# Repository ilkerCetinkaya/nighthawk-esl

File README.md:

# NIGHTHAWK: ESL security research instrument (KiCad hardware, firmware, AI-assisted routing)

**Role: Hardware and firmware designer** · Nov 2026 to present · work in progress

> 🇹🇷 **Özet:** NIGHTHAWK, elektronik raf etiketi (ESL) sistemlerinin güvenlik araştırması için tasarladığım taşınabilir bir ölçüm cihazı. REV A (ESP32-C3 + iki RF genişleme yuvası) şematik ve PCB olarak tamamlandı, üretilmedi. REV B, tek kartta 2.4 GHz + 868 MHz + 13.56 MHz NFC + IR bağlantısını birleştiren 80×50 mm, 4 katmanlı bir tasarım: şematik ve yerleşim tamam, **yönlendirme (routing) henüz tamamlanmadı**. Hiçbir kart üretilmedi, güç verilmedi, ölçülmedi. Bu depo her şeyi (şematikler, üretici betikleri, mühendislik raporları, firmware, masaüstü uygulaması ve AI destekli routing altyapısı) dürüst durum notlarıyla birlikte içerir.

> **Status, stated plainly:** nothing in this repository has been fabricated, powered up or measured. Every antenna, RF-matching and coexistence number is a datasheet value, a hand calculation or an assumption, and is labelled that way in the documents. No claim of antenna performance, RF compliance or production readiness is made. REV B routing is **not finished**, and the only REV B Gerber set published is an explicitly **unrouted, non-functional** one (see "REV B manufacturing files").

## What it is

A bench instrument for studying electronic shelf label (ESL) links on equipment you own, with the radio paths kept measurable (U.FL test points, tunable matching networks) and a **hardware interlock that keeps every RF path off by default**.

**Intended use:** owned equipment only, conducted or shielded testing, passive measurement. The firmware refuses to start a session when the hardware interlock is open. The repository contains **no ESL command generation** and no attack code; the research documents are desk research from public sources.

| Revision | State | What it is |
|---|---|---|
| **REV A** | schematic and PCB complete, ERC 0 violations, DRC 0 errors, not fabricated | ESP32-C3-WROOM-02 main board, two modular RF expansion slots, passive RF test path, hardware interlock |
| **REV B** | schematic and placement done, **routing in progress** | one integrated 80×50 mm 4-layer board: ESP32-C3, TI CC1352R (2.4 GHz and 868 MHz), TRF7970A NFC, 940 nm IR link, hardware interlock |

## REV B at a glance

| Block | Parts |
|---|---|
| **Controller** | ESP32-C3-WROOM-02 (on-board antenna keepout per Espressif, 15 mm) |
| **Sub-GHz and 2.4 GHz radio** | TI CC1352R1F3RGZR, Johanson 0900PC15A0036 IPC (2.4 GHz and sub-GHz from one RF port pair), 868 MHz chip antenna, 2.4 GHz inverted-F antenna (TI AN043 geometry), U.FL test connectors, tunable pi/L matching networks |
| **NFC** | TI TRF7970A, 18×16 mm 6-turn PCB coil (calculated 1.43 µH, not measured) |
| **Optical link** | 940 nm IR LED and photodiode |
| **Power** | LiPo, BQ24074 charger, TPS63802 buck-boost, USB-C |
| **Safety** | hardware interlock (default RF off), independent RF power gating, ESP32 to CC1352R time-slot coordination lines |
| **Fabrication target** | JLCPCB JLC04161H-7628 4-layer stackup, black mask, HASL with lead, cost-optimised |

<p align="center"><em>REV B 3D renders from KiCad (preliminary placement, not routed).</em></p>

### Engineering approach

Every document labels its evidence: **[DS]** manufacturer datasheet read, **[CALC]** calculation (script included), **[ASM]** assumption, **[MEAS]** measurement (none exist yet). Highlights:

- **Component gate and passive selection** for every RF part, with the datasheet pages used ([`REV_B_COMPONENT_GATE.md`](RevB/REV_B_COMPONENT_GATE.md), [`REV_B_PASSIVE_SELECTION.md`](RevB/REV_B_PASSIVE_SELECTION.md)).
- **RF design gate**: ESP32 to CC1352R coexistence, CC1352R input-power protection margins on a no-loss basis (the 1.3 dB discrepancy between two earlier tables is explained), 868 MHz corner keepout, NFC coil guidance, feed-line stackup ([`REV_B_RF_DESIGN_GATE.md`](RevB/REV_B_RF_DESIGN_GATE.md)).
- **Pre-routing resolutions**: USB-C and Johanson IPC footprints rebuilt from manufacturer drawings, battery connector and shield-frame dimensions checked ([`REV_B_PRE_ROUTING_RESOLUTIONS.md`](RevB/REV_B_PRE_ROUTING_RESOLUTIONS.md)).
- **Antenna design notes** with the TI AN043 inverted-F geometry and its keepouts on all four layers ([`REV_B_ANTENNA_ENGINEERING_R2.md`](RevB/REV_B_ANTENNA_ENGINEERING_R2.md)).
- **Mandatory prototype measurements** are listed rather than assumed away: S21 of the IPC path before the first transmission, antenna return loss, coil inductance and Q, time-slot coexistence.

### Routing status (honest)

- **Done and DRC-clean:** RF paths routed programmatically (`RevB/pcb/rf_route_b.py`): CC1352R to IPC differential pairs, both antenna feed chains with matching-network nodes, U.FL taps, ground vias. The 868 MHz feed uses a short B.Cu hop where the 2.4 GHz and sub-GHz feeds would otherwise cross.
- **Not done:** the rest of the board. With **In1 kept as a pure GND reference plane**, Freerouting 2.5.0 leaves about 200 nets unrouted on the current placement; allowing it to route on In1 reaches ~85 unrouted but breaks the plane, which is not acceptable here. The honest options are a looser placement or a larger board; that is a design decision still open.
- **Controlled impedance is not claimed.** The 50 Ω width (0.359 mm over L2, calculator result for the JLC stackup) is a number, not a validated geometry; the 2.4 GHz diff-pair necks are not 50 Ω.

## AI-assisted routing infrastructure (`RevB/ai_routing/`)

An experiment in driving KiCad and an autorouter through MCP, with engineering-grade checks instead of trust in the autorouter.

- **kicad-mcp-pro 4.9.0** and the **official Freerouting 2.5.0 MCP server**, run locally and offline (no design data leaves the machine).
- Tested on a copy, on a 16-net subset: both paths completed 20 of 20 connections (about 126 mm, 17 vias), **but** the router drew signal tracks on the GND plane and ignored custom DRC rules. Full report: [`RevB/ai_routing/REPORT.md`](RevB/ai_routing/REPORT.md).
- Problems found and documented: KiCad 10.0.6's CLI has no headless DSN export (pcbnew's Python API is used), kicad-mcp-pro's Freerouting command adds a `-drc` flag that makes 2.5.0 skip routing, Freerouting's MCP advertises an `outputSchema` but returns no `structuredContent` (a wrapper strips it), and one environment variable made kicad-mcp-pro hang at start-up.
- Recommended architecture: RF paths scripted and locked, the rest routed by class, and a gate that fails if any signal track appears on the GND plane.
- Handshake evidence and the continuing plan: `RevB/ai_routing/results/handshake_evidence.md`, `RevB/ai_routing/HANDOFF_PHASES.md`.

## Repository layout

| Path | Contents |
|---|---|
| `Hardware/` | REV A KiCad project (`NIGHTHAWK.kicad_pro`, 11 sheets, PCB) and `build/` generator scripts (`design.py` is the single source of parts and nets) |
| `Firmware/` | PlatformIO + ESP-IDF project: CLI over USB, interlock monitor, I/O expander, ADC, microSD, device database. Not compiled on hardware |
| `Software/desktop_app/` | PySide6 companion app |
| `Documentation/` | REV A reports, pin assignment, parts verification, race and watchdog reviews, `Research/` (ESL protocol desk research, TagTinker review, licence audit) |
| `RevB/` | REV B design documents, `schematic/` (7 sheets, generator scripts), `pcb/` (board generator, RF routing, routing and verification scripts), `integrated/` (RF calculations), `ai_routing/` |
| `README_REV_A.md` | the original REV A readme |

REV A manufacturing outputs and bulky generated test boards are deliberately not published. REV B has an **unrouted, non-functional** JLCPCB set under `RevB/manufacturing/` (see below).

## REV B manufacturing files (unrouted, non-functional)

`RevB/manufacturing/JLCPCB_REVB_UNROUTED/` holds the Gerber zip, a JLCPCB BOM with LCSC numbers (181 parts, none invented) and a CPL with corrected rotations, generated by `RevB/manufacturing/make_fab_b.py` from the board as it stands. **The board is not routed (409 unconnected connections), so these files would produce a non-working PCB.** They were generated on request to exercise the fabrication pipeline.

- CPL rotation: KiCad angle, bottom side `(180 - angle) mod 360`, plus package corrections from the community JLCKicadTools database (not an official JLCPCB table). Polarised parts without a matching rule (ESP32 module, CC1352R, TRF7970A, LEDs, crystals, IR parts, USB-C) must be checked in the JLCPCB preview.
- Parts without an LCSC number (Johanson IPC, shield frame and others) and all DNP matching parts are listed separately in `NOT_ASSEMBLED_BY_JLCPCB.csv`.
- Placement was loosened (0.6 mm extra courtyard gap, more use of the bottom side) to try to route with In1 kept as a pure GND plane; Freerouting still left roughly 110 to 140 connections open. Details in `RevB/ai_routing/REPORT.md`.

## Rebuild (REV B)

Run with KiCad 10's bundled Python:

```
cd RevB/schematic && python3 gen_footprints_b.py && python3 gen_sch_b.py
cd ../pcb && python3 make_board_b.py      # board with placement
python3 rf_route_b.py                      # programmatic RF routing
python3 verify_r2.py                       # keepout verification on all layers
```

## What is not done

Routing of the full REV B board · antenna and matching validation · any measurement · firmware on hardware · a releasable (routed, reviewed) REV B Gerber set · RF compliance. Each of these is an open item, not a hidden assumption.

---

*Product and component names belong to their owners (Espressif, Texas Instruments, Johanson Technology, Würth Elektronik, JST, JLCPCB and others). The research notes cite public sources (Furrtek, PrecIR, TagTinker); their licences are audited in `Documentation/Research/REUSE_AND_LICENSE_AUDIT.md`. No licence is granted for this repository yet; all rights reserved by the author until one is chosen.*

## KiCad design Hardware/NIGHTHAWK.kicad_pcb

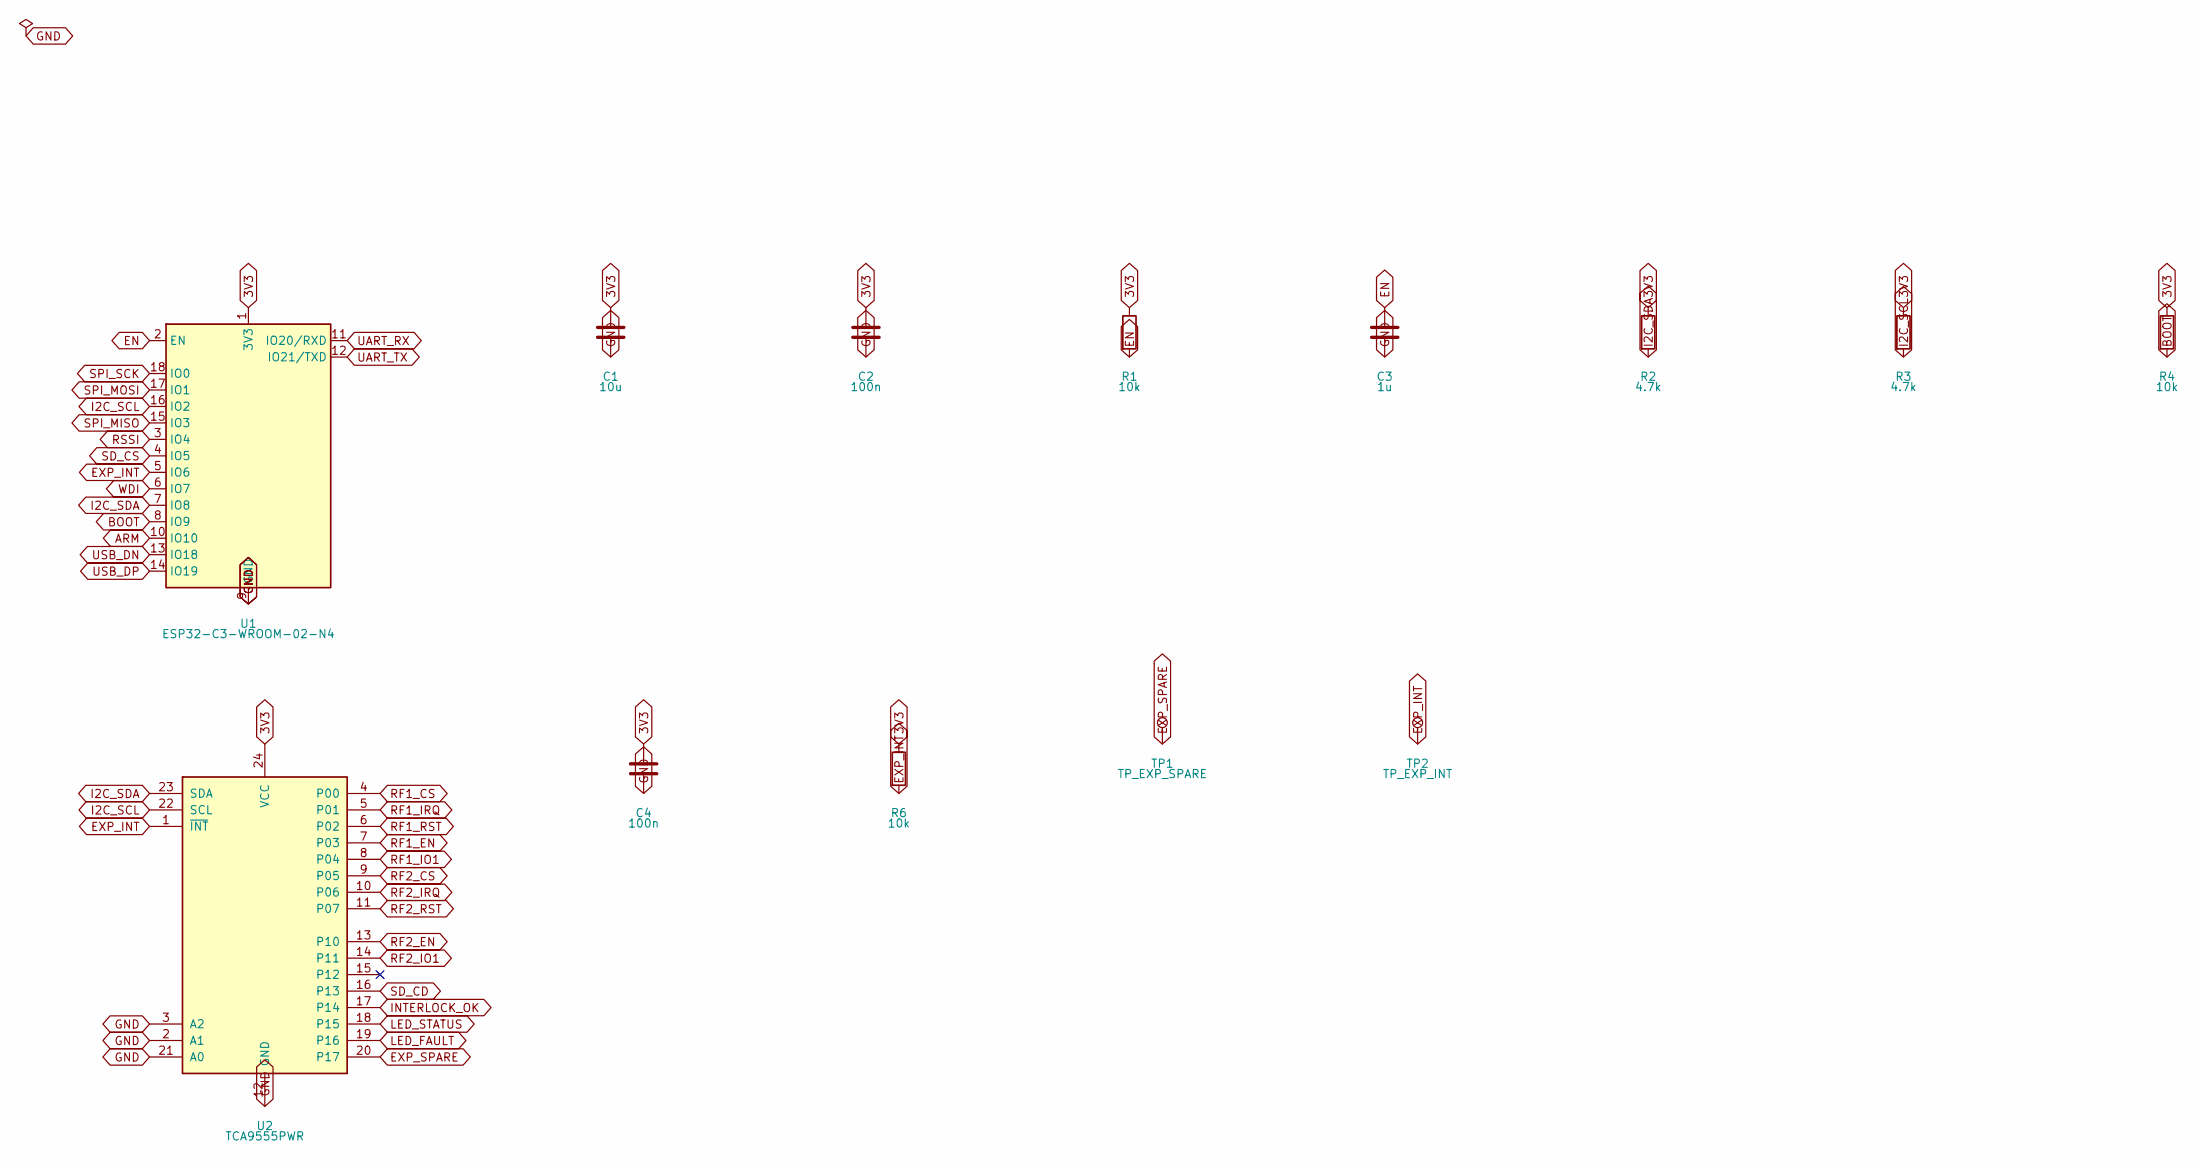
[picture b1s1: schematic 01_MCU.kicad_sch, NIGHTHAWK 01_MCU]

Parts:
C1: 10u; C_0603_1608Metric; MPN CL10A106KP8NNNC; LCSC C19702
C2, C4: 100n; C_0603_1608Metric; MPN CC0603KRX7R7BB104; LCSC C108079
C3: 1u; C_0603_1608Metric; MPN CL10A105KB8NNNC; LCSC C15849
R1, R4, R6: 10k; R_0603_1608Metric; MPN 0603WAF1002T5E; LCSC C25804
R2, R3: 4.7k; R_0603_1608Metric; MPN 0603WAF4701T5E; LCSC C23162
TP1: TP_EXP_SPARE; TestPoint_Pad_D1.5mm
TP2: TP_EXP_INT; TestPoint_Pad_D1.5mm
U1: ESP32-C3-WROOM-02-N4; ESP32-C3-WROOM-02; MPN ESP32-C3-WROOM-02-N4; LCSC C2934560
U2: TCA9555PWR; TSSOP-24_4.4x7.8mm_P0.65mm; MPN TCA9555PWR; LCSC C465732

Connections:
3V3: C1.1, C2.1, C4.1, R1.1, R2.1, R3.1, R4.1, R6.1, U1.1 (3V3), U2.24 (VCC); also elsewhere on the board
ARM: U1.10 (IO10); also elsewhere on the board
BOOT: R4.2, U1.8 (IO9); also elsewhere on the board
EN: C3.1, R1.2, U1.2 (EN); also elsewhere on the board
EXP_INT: R6.2, TP2.1, U1.5 (IO6), U2.1 (~INT)
EXP_SPARE: TP1.1, U2.20 (P17)
GND: C1.2, C2.2, C3.2, C4.2, U1.9 (GND), U1.19 (GND), U2.2 (A1), U2.3 (A2), U2.12 (GND), U2.21 (A0); also elsewhere on the board
I2C_SCL: R3.2, U1.16 (IO2), U2.22 (SCL); also elsewhere on the board
I2C_SDA: R2.2, U1.7 (IO8), U2.23 (SDA); also elsewhere on the board
INTERLOCK_OK: U2.17 (P14); also elsewhere on the board
LED_FAULT: U2.19 (P16); also elsewhere on the board
LED_STATUS: U2.18 (P15); also elsewhere on the board
RF1_CS: U2.4 (P00); also elsewhere on the board
RF1_EN: U2.7 (P03); also elsewhere on the board
RF1_IO1: U2.8 (P04); also elsewhere on the board
RF1_IRQ: U2.5 (P01); also elsewhere on the board
RF1_RST: U2.6 (P02); also elsewhere on the board
RF2_CS: U2.9 (P05); also elsewhere on the board
RF2_EN: U2.13 (P10); also elsewhere on the board
RF2_IO1: U2.14 (P11); also elsewhere on the board
RF2_IRQ: U2.10 (P06); also elsewhere on the board
RF2_RST: U2.11 (P07); also elsewhere on the board
RSSI: U1.3 (IO4); also elsewhere on the board
SD_CD: U2.16 (P13); also elsewhere on the board
SD_CS: U1.4 (IO5); also elsewhere on the board
SPI_MISO: U1.15 (IO3); also elsewhere on the board
SPI_MOSI: U1.17 (IO1); also elsewhere on the board
SPI_SCK: U1.18 (IO0); also elsewhere on the board
UART_RX: U1.11 (IO20/RXD); also elsewhere on the board
UART_TX: U1.12 (IO21/TXD); also elsewhere on the board
USB_DN: U1.13 (IO18); also elsewhere on the board
USB_DP: U1.14 (IO19); also elsewhere on the board
WDI: U1.6 (IO7); also elsewhere on the board

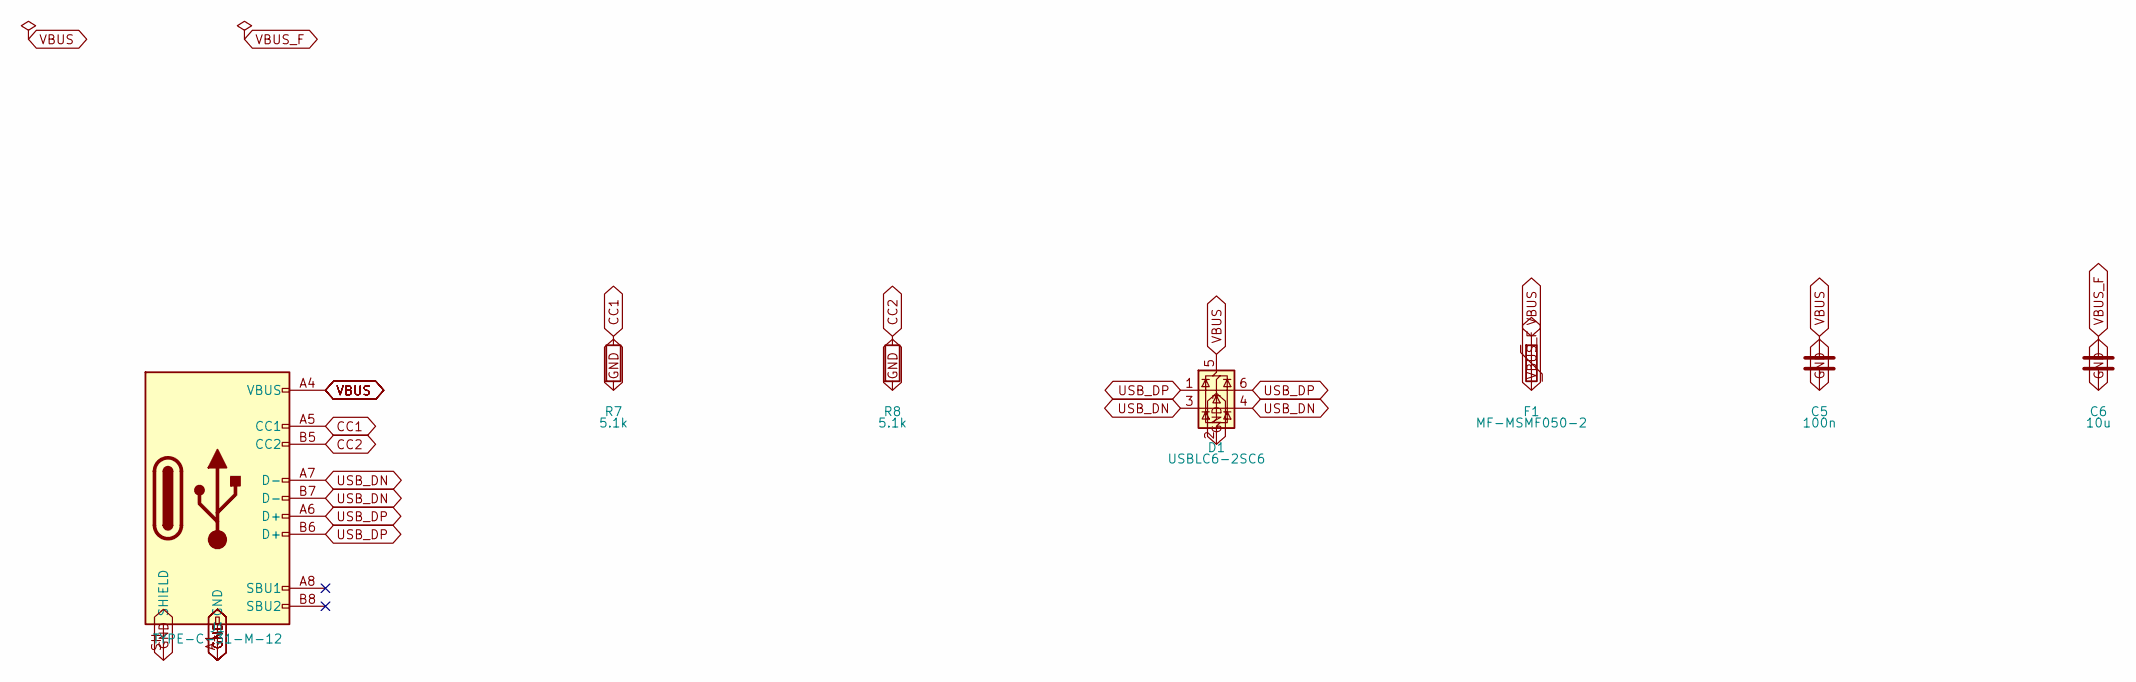
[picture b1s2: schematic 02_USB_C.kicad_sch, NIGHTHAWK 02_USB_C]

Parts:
C5: 100n; C_0603_1608Metric; MPN CC0603KRX7R7BB104; LCSC C108079
C6: 10u; C_0603_1608Metric; MPN CL10A106KP8NNNC; LCSC C19702
D1: USBLC6-2SC6; SOT-23-6; MPN USBLC6-2SC6; LCSC C7519
F1: MF-MSMF050-2; Fuse_1812_4532Metric; MPN MF-MSMF050-2; LCSC C17313
J1: TYPE-C-31-M-12; USB_C_Receptacle_HRO_TYPE-C-31-M-12; MPN TYPE-C-31-M-12; LCSC C165948
R7, R8: 5.1k; R_0603_1608Metric; MPN 0603WAF5101T5E; LCSC C23186

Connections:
CC1: J1.A5 (CC1), R7.1
CC2: J1.B5 (CC2), R8.1
GND: C5.2, C6.2, D1.2 (GND), J1.A1 (GND), J1.A12 (GND), J1.B1 (GND), J1.B12 (GND), J1.SH (SHIELD), R7.2, R8.2; also elsewhere on the board
USB_DN: D1.3 (I/O2), D1.4 (I/O2), J1.A7 (D-), J1.B7 (D-); also elsewhere on the board
USB_DP: D1.1 (I/O1), D1.6 (I/O1), J1.A6 (D+), J1.B6 (D+); also elsewhere on the board
VBUS: C5.1, D1.5 (VBUS), F1.1, J1.A4 (VBUS), J1.A9 (VBUS), J1.B4 (VBUS), J1.B9 (VBUS)
VBUS_F: C6.1, F1.2; also elsewhere on the board

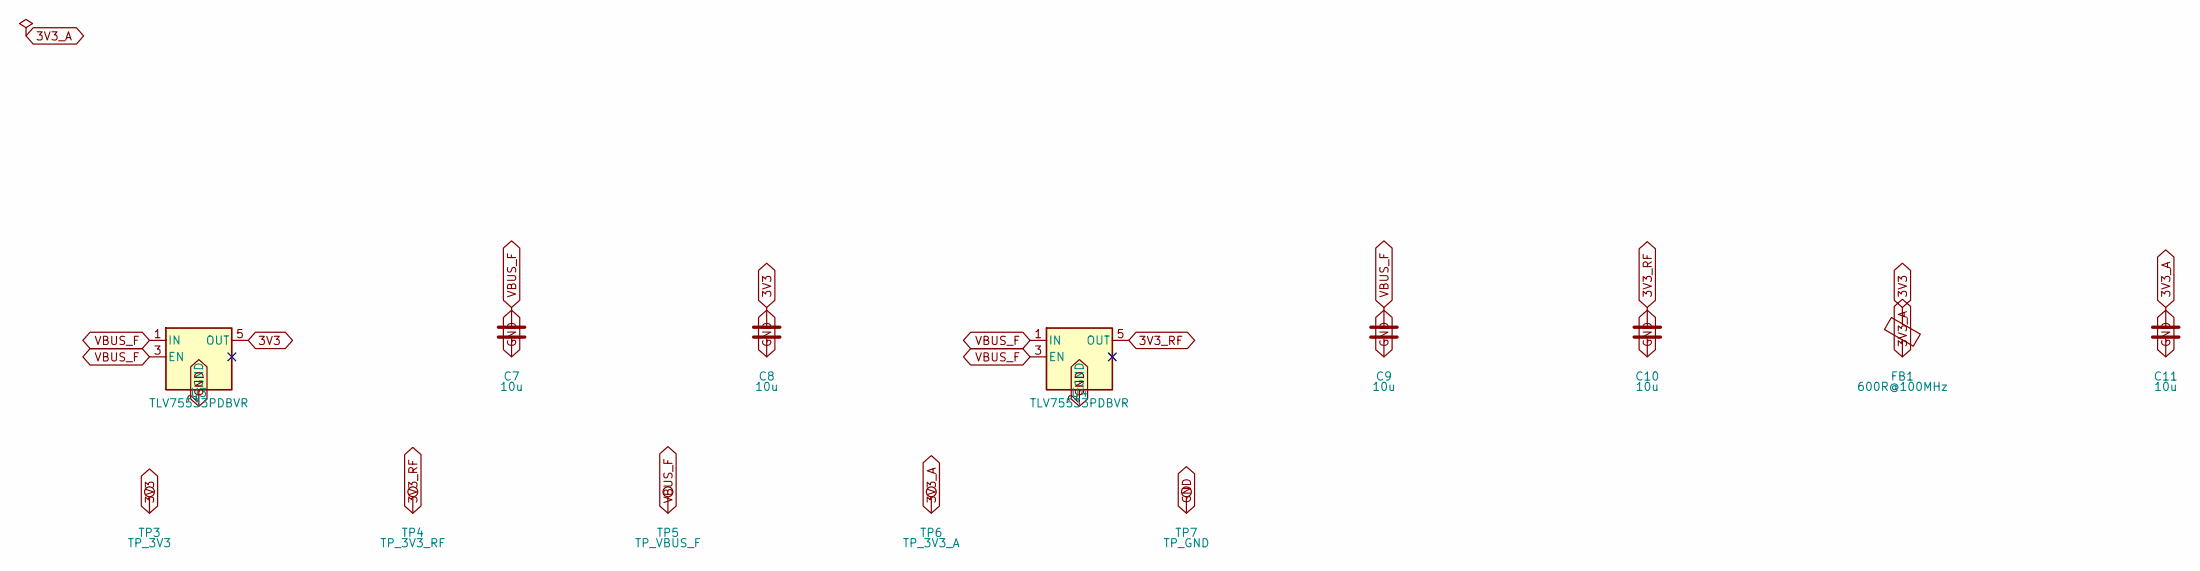
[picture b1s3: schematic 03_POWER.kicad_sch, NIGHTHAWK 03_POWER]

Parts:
C7, C8, C9, C10, C11: 10u; C_0603_1608Metric; MPN CL10A106KP8NNNC; LCSC C19702
FB1: 600R@100MHz; L_0603_1608Metric; MPN BLM18AG601SN1D; LCSC C19330
TP3: TP_3V3; TestPoint_Pad_D1.5mm
TP4: TP_3V3_RF; TestPoint_Pad_D1.5mm
TP5: TP_VBUS_F; TestPoint_Pad_D1.5mm
TP6: TP_3V3_A; TestPoint_Pad_D1.5mm
TP7: TP_GND; TestPoint_Pad_D1.5mm
U3, U4: TLV75533PDBVR; SOT-23-5; MPN TLV75533PDBVR; LCSC C404027

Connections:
3V3: C8.1, FB1.1, TP3.1, U3.5 (OUT); also elsewhere on the board
3V3_A: C11.1, FB1.2, TP6.1
3V3_RF: C10.1, TP4.1, U4.5 (OUT); also elsewhere on the board
GND: C7.2, C8.2, C9.2, C10.2, C11.2, TP7.1, U3.2 (GND), U4.2 (GND); also elsewhere on the board
VBUS_F: C7.1, C9.1, TP5.1, U3.1 (IN), U3.3 (EN), U4.1 (IN), U4.3 (EN); also elsewhere on the board

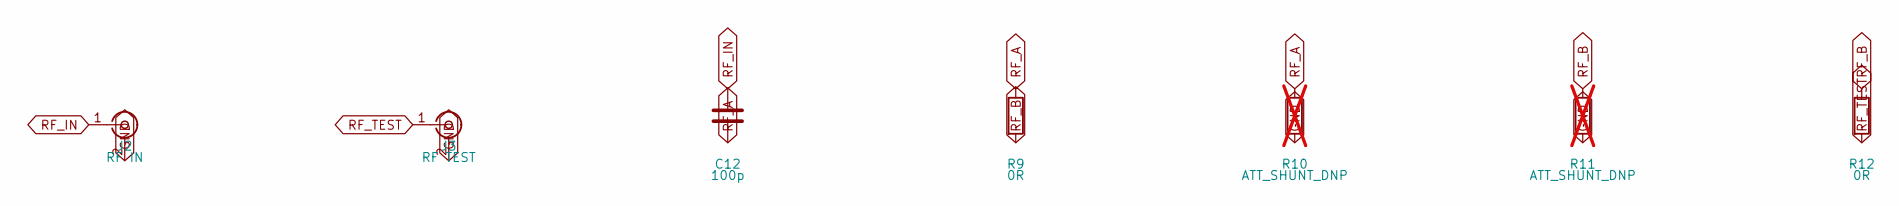
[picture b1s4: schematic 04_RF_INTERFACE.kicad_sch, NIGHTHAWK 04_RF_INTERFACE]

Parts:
C12: 100p; C_0603_1608Metric; MPN CL10C101JB8NNNC; LCSC C14858
J2: RF IN; SMA_Samtec_SMA-J-P-H-ST-EM1_EdgeMount; MPN SMA-J-P-H-ST-EM1; LCSC C5199907
J3: RF TEST; SMA_Samtec_SMA-J-P-H-ST-EM1_EdgeMount; MPN SMA-J-P-H-ST-EM1; LCSC C5199907
R9, R12: 0R; R_0603_1608Metric; MPN 0603WAF0000T5E; LCSC C21189
R10, R11: ATT_SHUNT_DNP; R_0603_1608Metric; not fitted

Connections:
GND: J2.2 (Ext), J3.2 (Ext), R10.2, R11.2; also elsewhere on the board
RF_A: C12.2, R9.1, R10.1
RF_B: R9.2, R11.1, R12.1
RF_IN: C12.1, J2.1 (In)
RF_TEST: J3.1 (In), R12.2

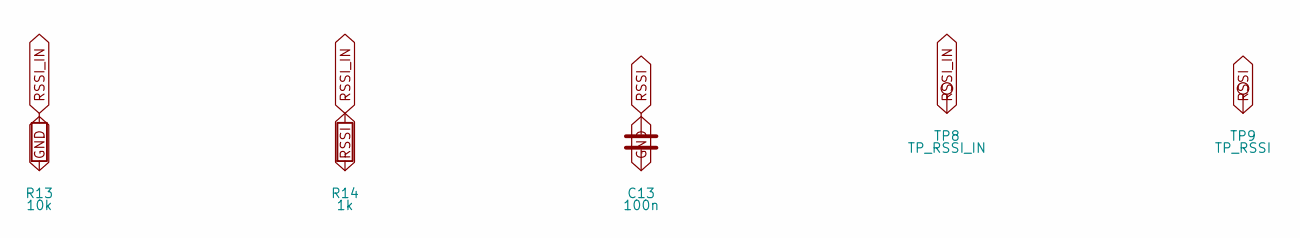
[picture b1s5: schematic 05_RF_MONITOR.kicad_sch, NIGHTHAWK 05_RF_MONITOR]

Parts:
C13: 100n; C_0603_1608Metric; MPN CC0603KRX7R7BB104; LCSC C108079
R13: 10k; R_0603_1608Metric; MPN 0603WAF1002T5E; LCSC C25804
R14: 1k; R_0603_1608Metric; MPN 0603WAF1001T5E; LCSC C21190
TP8: TP_RSSI_IN; TestPoint_Pad_D1.5mm
TP9: TP_RSSI; TestPoint_Pad_D1.5mm

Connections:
GND: C13.2, R13.2; also elsewhere on the board
RSSI: C13.1, R14.2, TP9.1; also elsewhere on the board
RSSI_IN: R13.1, R14.1, TP8.1

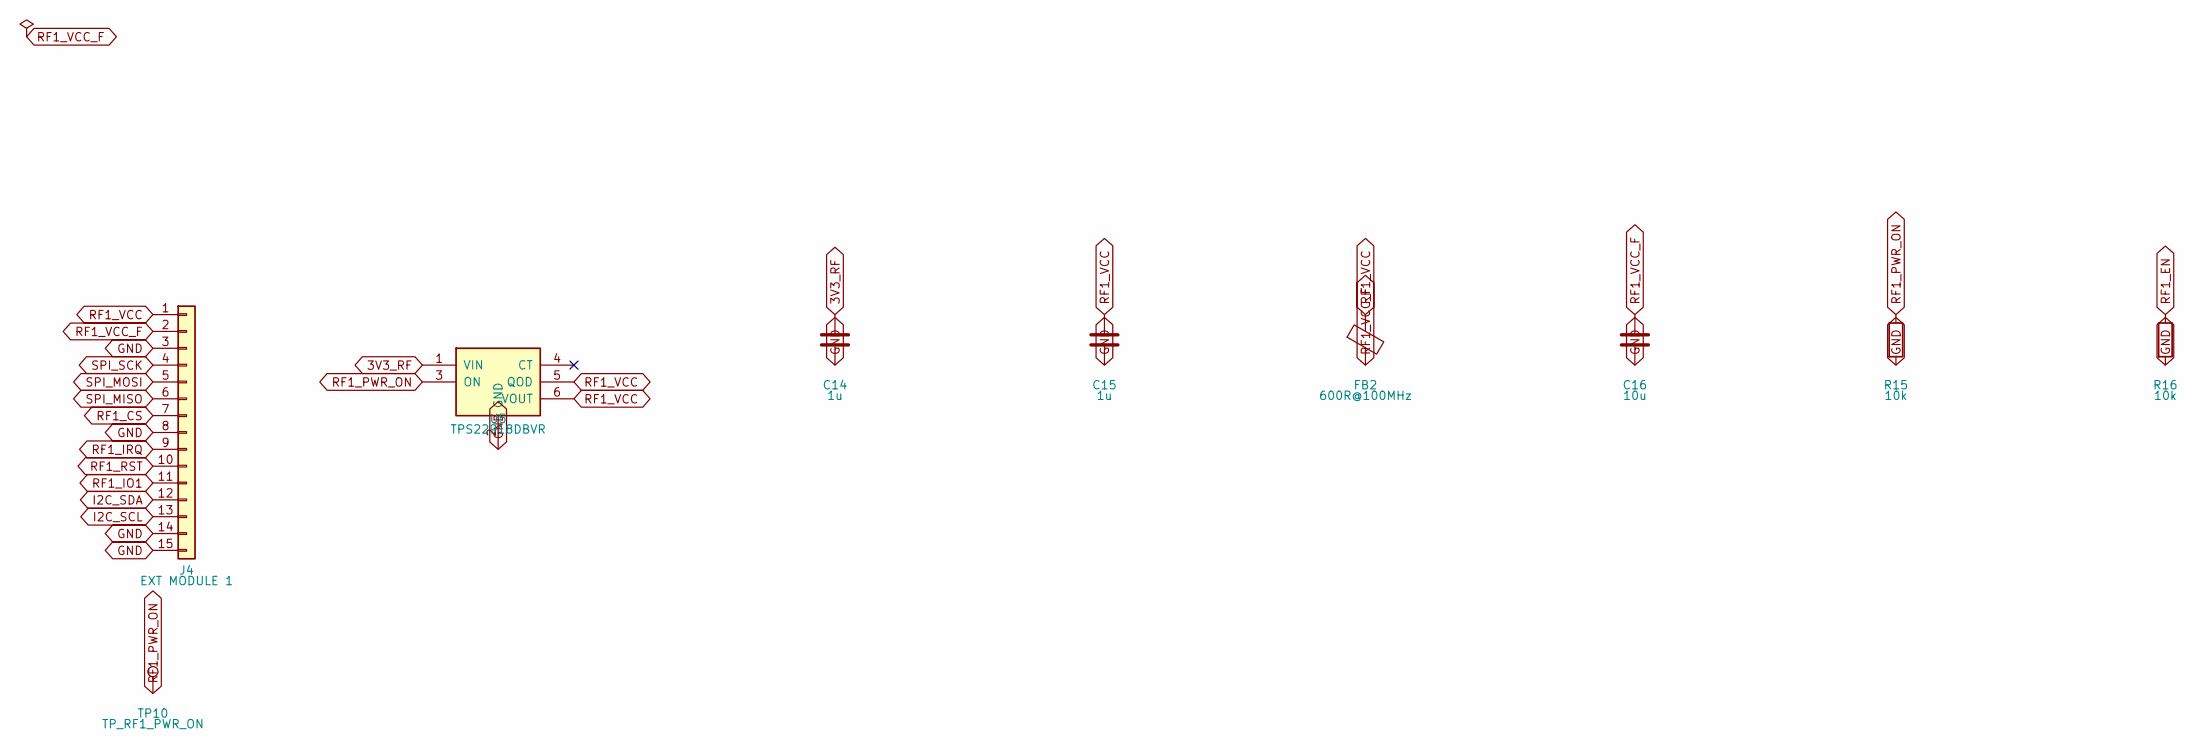
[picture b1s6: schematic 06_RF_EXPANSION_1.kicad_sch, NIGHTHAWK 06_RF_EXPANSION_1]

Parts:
C14, C15: 1u; C_0603_1608Metric; MPN CL10A105KB8NNNC; LCSC C15849
C16: 10u; C_0603_1608Metric; MPN CL10A106KP8NNNC; LCSC C19702
FB2: 600R@100MHz; L_0603_1608Metric; MPN BLM18AG601SN1D; LCSC C19330
J4: EXT MODULE 1; JST_SH_SM15B-SRSS-TB_1x15-1MP_P1.00mm_Horizontal; MPN SM15B-SRSS-TB(LF)(SN); LCSC C160414
R15, R16: 10k; R_0603_1608Metric; MPN 0603WAF1002T5E; LCSC C25804
TP10: TP_RF1_PWR_ON; TestPoint_Pad_D1.5mm
U5: TPS22918DBVR; SOT-23-6; MPN TPS22918DBVR; LCSC C131941

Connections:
3V3_RF: C14.1, U5.1 (VIN); also elsewhere on the board
GND: C14.2, C15.2, C16.2, J4.3, J4.8, J4.14, J4.15, J4.MP, R15.2, R16.2, U5.2 (GND); also elsewhere on the board
I2C_SCL: J4.13; also elsewhere on the board
I2C_SDA: J4.12; also elsewhere on the board
RF1_CS: J4.7; also elsewhere on the board
RF1_EN: R16.1; also elsewhere on the board
RF1_IO1: J4.11; also elsewhere on the board
RF1_IRQ: J4.9; also elsewhere on the board
RF1_PWR_ON: R15.1, TP10.1, U5.3 (ON); also elsewhere on the board
RF1_RST: J4.10; also elsewhere on the board
RF1_VCC: C15.1, FB2.1, J4.1, U5.5 (QOD), U5.6 (VOUT)
RF1_VCC_F: C16.1, FB2.2, J4.2
SPI_MISO: J4.6; also elsewhere on the board
SPI_MOSI: J4.5; also elsewhere on the board
SPI_SCK: J4.4; also elsewhere on the board

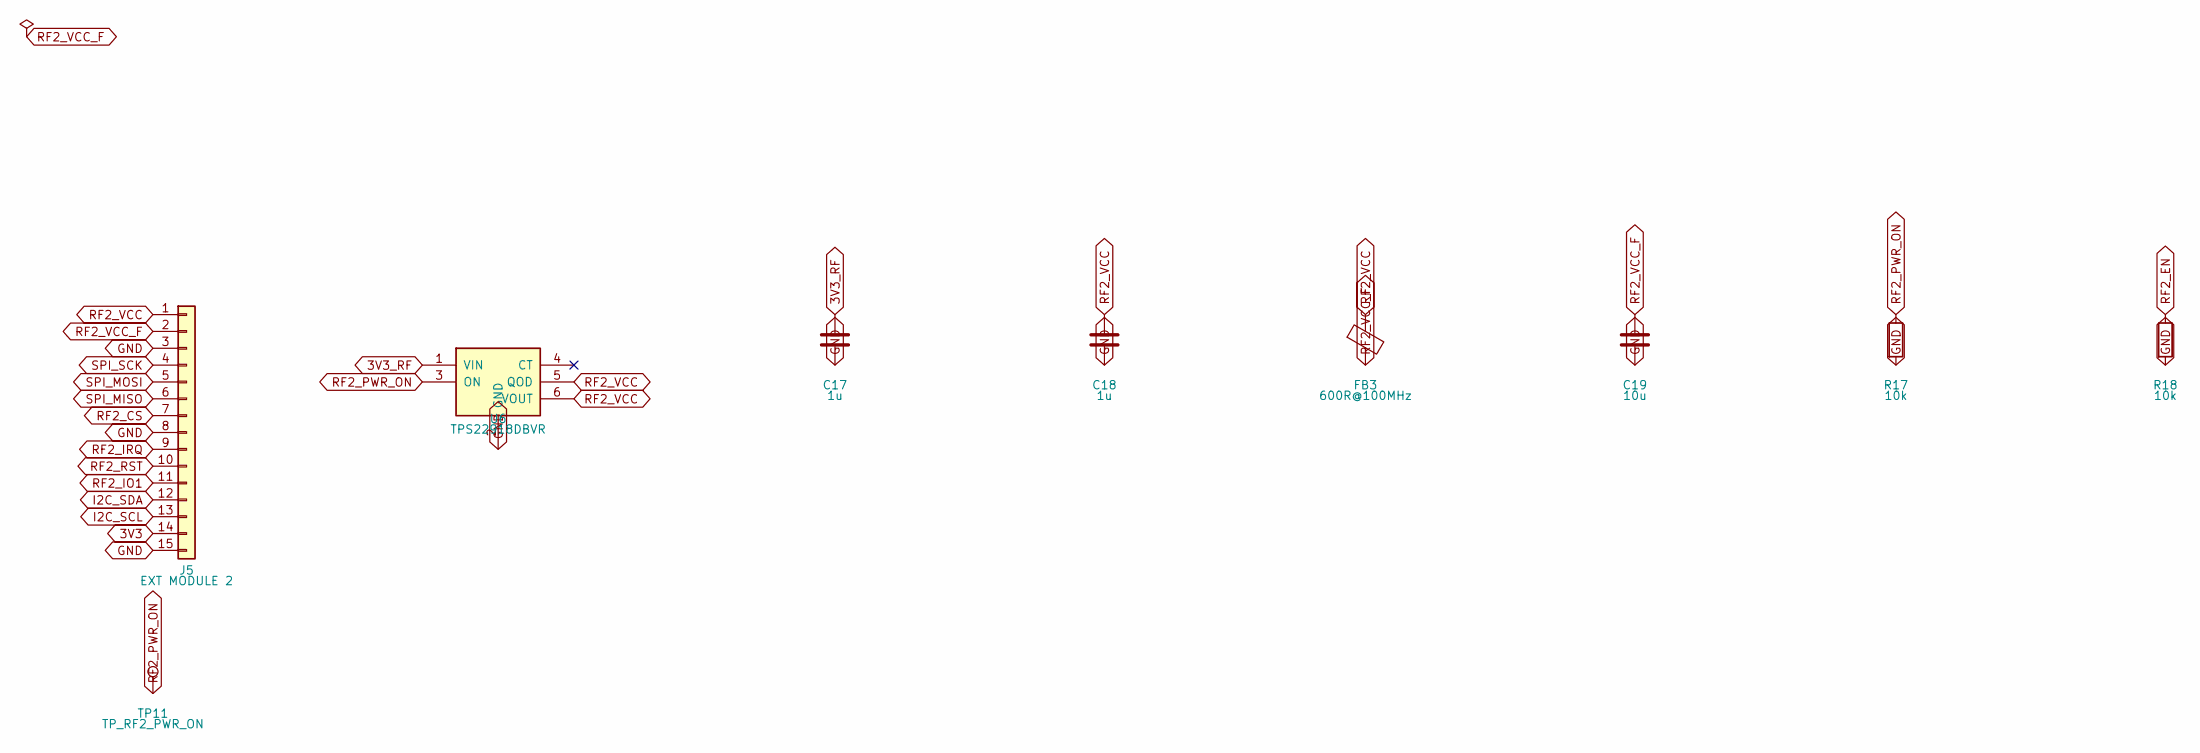
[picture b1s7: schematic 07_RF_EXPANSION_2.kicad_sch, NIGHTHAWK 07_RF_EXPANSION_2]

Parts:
C17, C18: 1u; C_0603_1608Metric; MPN CL10A105KB8NNNC; LCSC C15849
C19: 10u; C_0603_1608Metric; MPN CL10A106KP8NNNC; LCSC C19702
FB3: 600R@100MHz; L_0603_1608Metric; MPN BLM18AG601SN1D; LCSC C19330
J5: EXT MODULE 2; JST_SH_SM15B-SRSS-TB_1x15-1MP_P1.00mm_Horizontal; MPN SM15B-SRSS-TB(LF)(SN); LCSC C160414
R17, R18: 10k; R_0603_1608Metric; MPN 0603WAF1002T5E; LCSC C25804
TP11: TP_RF2_PWR_ON; TestPoint_Pad_D1.5mm
U6: TPS22918DBVR; SOT-23-6; MPN TPS22918DBVR; LCSC C131941

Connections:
3V3: J5.14; also elsewhere on the board
3V3_RF: C17.1, U6.1 (VIN); also elsewhere on the board
GND: C17.2, C18.2, C19.2, J5.3, J5.8, J5.15, J5.MP, R17.2, R18.2, U6.2 (GND); also elsewhere on the board
I2C_SCL: J5.13; also elsewhere on the board
I2C_SDA: J5.12; also elsewhere on the board
RF2_CS: J5.7; also elsewhere on the board
RF2_EN: R18.1; also elsewhere on the board
RF2_IO1: J5.11; also elsewhere on the board
RF2_IRQ: J5.9; also elsewhere on the board
RF2_PWR_ON: R17.1, TP11.1, U6.3 (ON); also elsewhere on the board
RF2_RST: J5.10; also elsewhere on the board
RF2_VCC: C18.1, FB3.1, J5.1, U6.5 (QOD), U6.6 (VOUT)
RF2_VCC_F: C19.1, FB3.2, J5.2
SPI_MISO: J5.6; also elsewhere on the board
SPI_MOSI: J5.5; also elsewhere on the board
SPI_SCK: J5.4; also elsewhere on the board

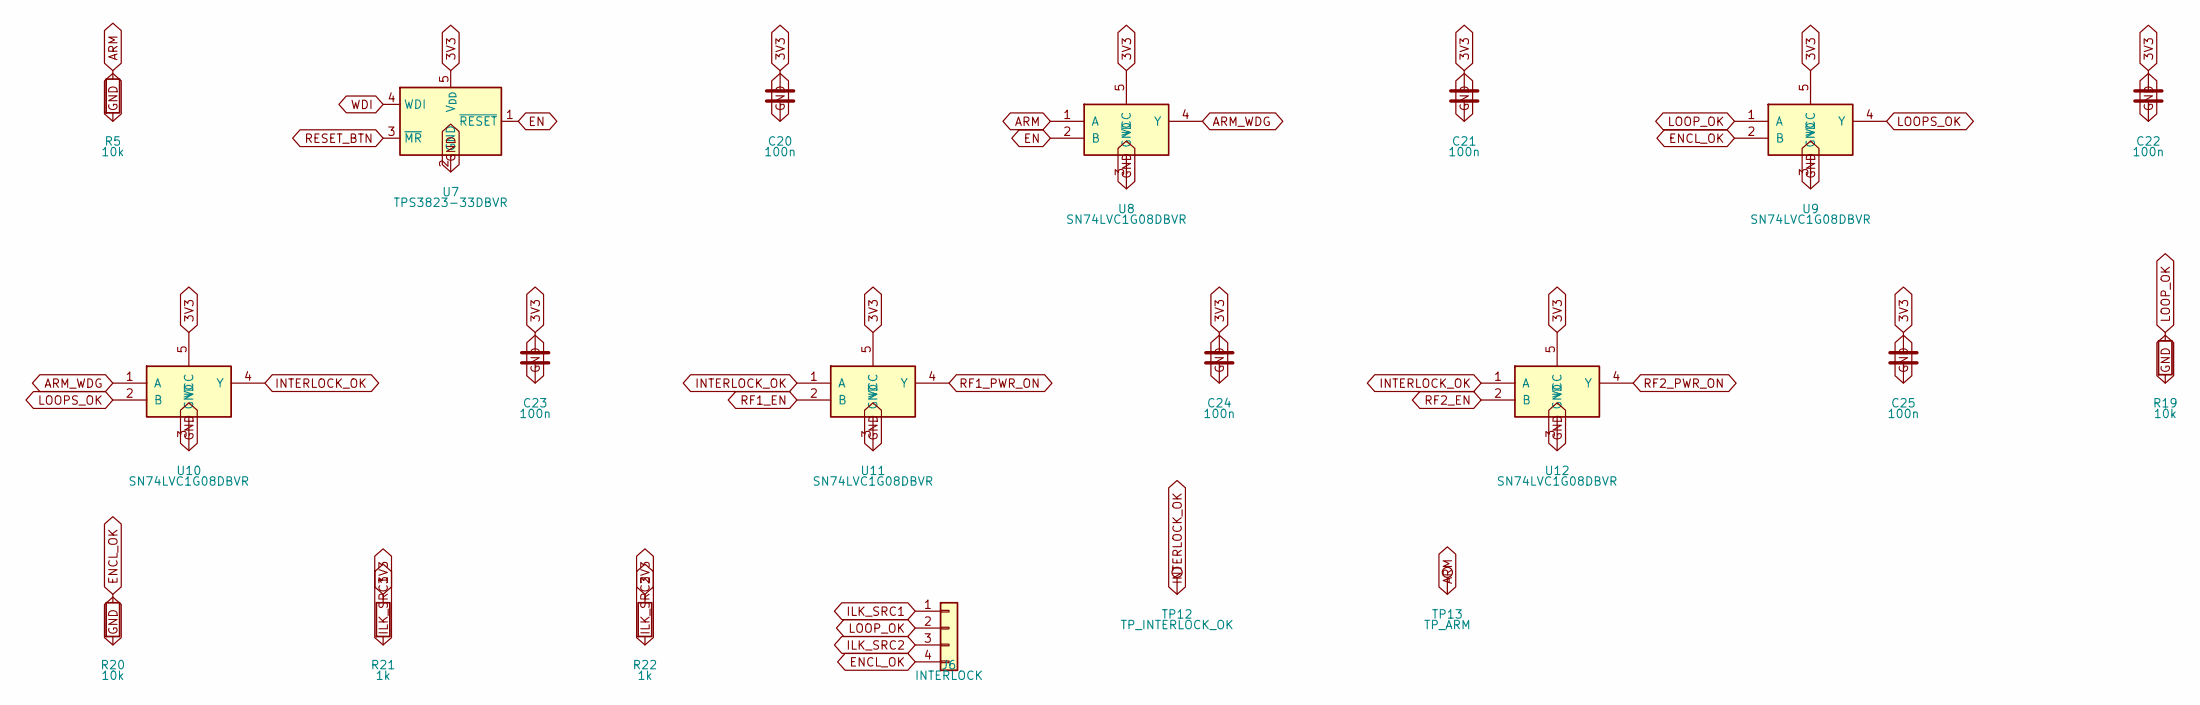
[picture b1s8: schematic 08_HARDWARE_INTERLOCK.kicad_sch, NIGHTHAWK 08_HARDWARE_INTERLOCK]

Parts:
C20, C21, C22, C23, C24, C25: 100n; C_0603_1608Metric; MPN CC0603KRX7R7BB104; LCSC C108079
J6: INTERLOCK; PinHeader_1x04_P2.54mm_Vertical; MPN PZ254V-11-04P; LCSC C2691448
R5, R19, R20: 10k; R_0603_1608Metric; MPN 0603WAF1002T5E; LCSC C25804
R21, R22: 1k; R_0603_1608Metric; MPN 0603WAF1001T5E; LCSC C21190
TP12: TP_INTERLOCK_OK; TestPoint_Pad_D1.5mm
TP13: TP_ARM; TestPoint_Pad_D1.5mm
U7: TPS3823-33DBVR; SOT-23-5; MPN TPS3823-33DBVR; LCSC C7719
U8, U9, U10, U11, U12: SN74LVC1G08DBVR; SOT-23-5; MPN SN74LVC1G08DBVR; LCSC C7666

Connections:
3V3: C20.1, C21.1, C22.1, C23.1, C24.1, C25.1, R21.1, R22.1, U7.5 (V_{DD}), U8.5 (VCC), U9.5 (VCC), U10.5 (VCC), U11.5 (VCC), U12.5 (VCC); also elsewhere on the board
ARM: R5.1, TP13.1, U8.1 (A); also elsewhere on the board
ARM_WDG: U8.4 (Y), U10.1 (A)
EN: U7.1 (~RESET), U8.2 (B); also elsewhere on the board
ENCL_OK: J6.4, R20.1, U9.2 (B)
GND: C20.2, C21.2, C22.2, C23.2, C24.2, C25.2, R5.2, R19.2, R20.2, U7.2 (GND), U8.3 (GND), U9.3 (GND), U10.3 (GND), U11.3 (GND), U12.3 (GND); also elsewhere on the board
ILK_SRC1: J6.1, R21.2
ILK_SRC2: J6.3, R22.2
INTERLOCK_OK: TP12.1, U10.4 (Y), U11.1 (A), U12.1 (A); also elsewhere on the board
LOOPS_OK: U9.4 (Y), U10.2 (B)
LOOP_OK: J6.2, R19.1, U9.1 (A)
RESET_BTN: U7.3 (~MR); also elsewhere on the board
RF1_EN: U11.2 (B); also elsewhere on the board
RF1_PWR_ON: U11.4 (Y); also elsewhere on the board
RF2_EN: U12.2 (B); also elsewhere on the board
RF2_PWR_ON: U12.4 (Y); also elsewhere on the board
WDI: U7.4 (WDI); also elsewhere on the board

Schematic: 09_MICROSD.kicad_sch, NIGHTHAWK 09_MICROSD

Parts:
C26: 10u; C_0603_1608Metric; MPN CL10A106KP8NNNC; LCSC C19702
C27: 100n; C_0603_1608Metric; MPN CC0603KRX7R7BB104; LCSC C108079
J7: microSD; microSD_HC_Hirose_DM3AT-SF-PEJM5; MPN DM3AT-SF-PEJM5; LCSC C114218
R23, R24, R25, R26: 10k; R_0603_1608Metric; MPN 0603WAF1002T5E; LCSC C25804

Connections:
3V3: C26.1, C27.1, J7.4 (VDD), R23.1, R24.1, R25.1, R26.1; also elsewhere on the board
GND: C26.2, C27.2, J7.6 (VSS), J7.10 (DET_A), J7.SH (SHIELD); also elsewhere on the board
SD_CD: J7.9 (DET_B), R26.2; also elsewhere on the board
SD_CS: J7.2 (DAT3/CD), R25.2; also elsewhere on the board
SD_DAT1: J7.8 (DAT1), R24.2
SD_DAT2: J7.1 (DAT2), R23.2
SPI_MISO: J7.7 (DAT0); also elsewhere on the board
SPI_MOSI: J7.3 (CMD); also elsewhere on the board
SPI_SCK: J7.5 (CLK); also elsewhere on the board

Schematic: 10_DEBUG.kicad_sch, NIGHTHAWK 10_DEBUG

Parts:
J8: UART; PinHeader_1x04_P2.54mm_Vertical; MPN PZ254V-11-04P; LCSC C2691448
J9: DEBUG; PinHeader_1x04_P2.54mm_Vertical; MPN PZ254V-11-04P; LCSC C2691448
SW1: RESET; SW_SPST_PTS810; MPN PTS810SJG250SMTRLFS; LCSC C221895
SW2: BOOT; SW_SPST_PTS810; MPN PTS810SJG250SMTRLFS; LCSC C221895

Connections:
3V3: J8.2, J9.2; also elsewhere on the board
BOOT: J9.4, SW2.1; also elsewhere on the board
EN: J9.3; also elsewhere on the board
GND: J8.1, J9.1, SW1.2, SW2.2; also elsewhere on the board
RESET_BTN: SW1.1; also elsewhere on the board
UART_RX: J8.4; also elsewhere on the board
UART_TX: J8.3; also elsewhere on the board

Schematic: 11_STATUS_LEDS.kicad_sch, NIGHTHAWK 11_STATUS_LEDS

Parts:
D2, D3: GREEN; LED_0603_1608Metric; MPN GL0603UG01; LCSC C51933293
D4: WHITE; LED_0603_1608Metric; MPN GL0603UW01; LCSC C51933297
D5: RED; LED_0603_1608Metric; MPN KT-0603R; LCSC C2286
R27, R28, R29, R30: 1k; R_0603_1608Metric; MPN 0603WAF1001T5E; LCSC C21190

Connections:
3V3: R27.1; also elsewhere on the board
GND: D2.1 (K), D3.1 (K), D4.1 (K), D5.1 (K); also elsewhere on the board
INTERLOCK_OK: R28.1; also elsewhere on the board
LEDA_led_f: D5.2 (A), R30.2
LEDA_led_ilk: D3.2 (A), R28.2
LEDA_led_pwr: D2.2 (A), R27.2
LEDA_led_st: D4.2 (A), R29.2
LED_FAULT: R30.1; also elsewhere on the board
LED_STATUS: R29.1; also elsewhere on the board
